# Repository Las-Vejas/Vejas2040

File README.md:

# Vejas2040
an RP2040 devboard made by me

What it includes:
- RP2040
- 1 Neopixel LED
- 2 buttons
- a pico form factor

Here are some images of the board (3d files):

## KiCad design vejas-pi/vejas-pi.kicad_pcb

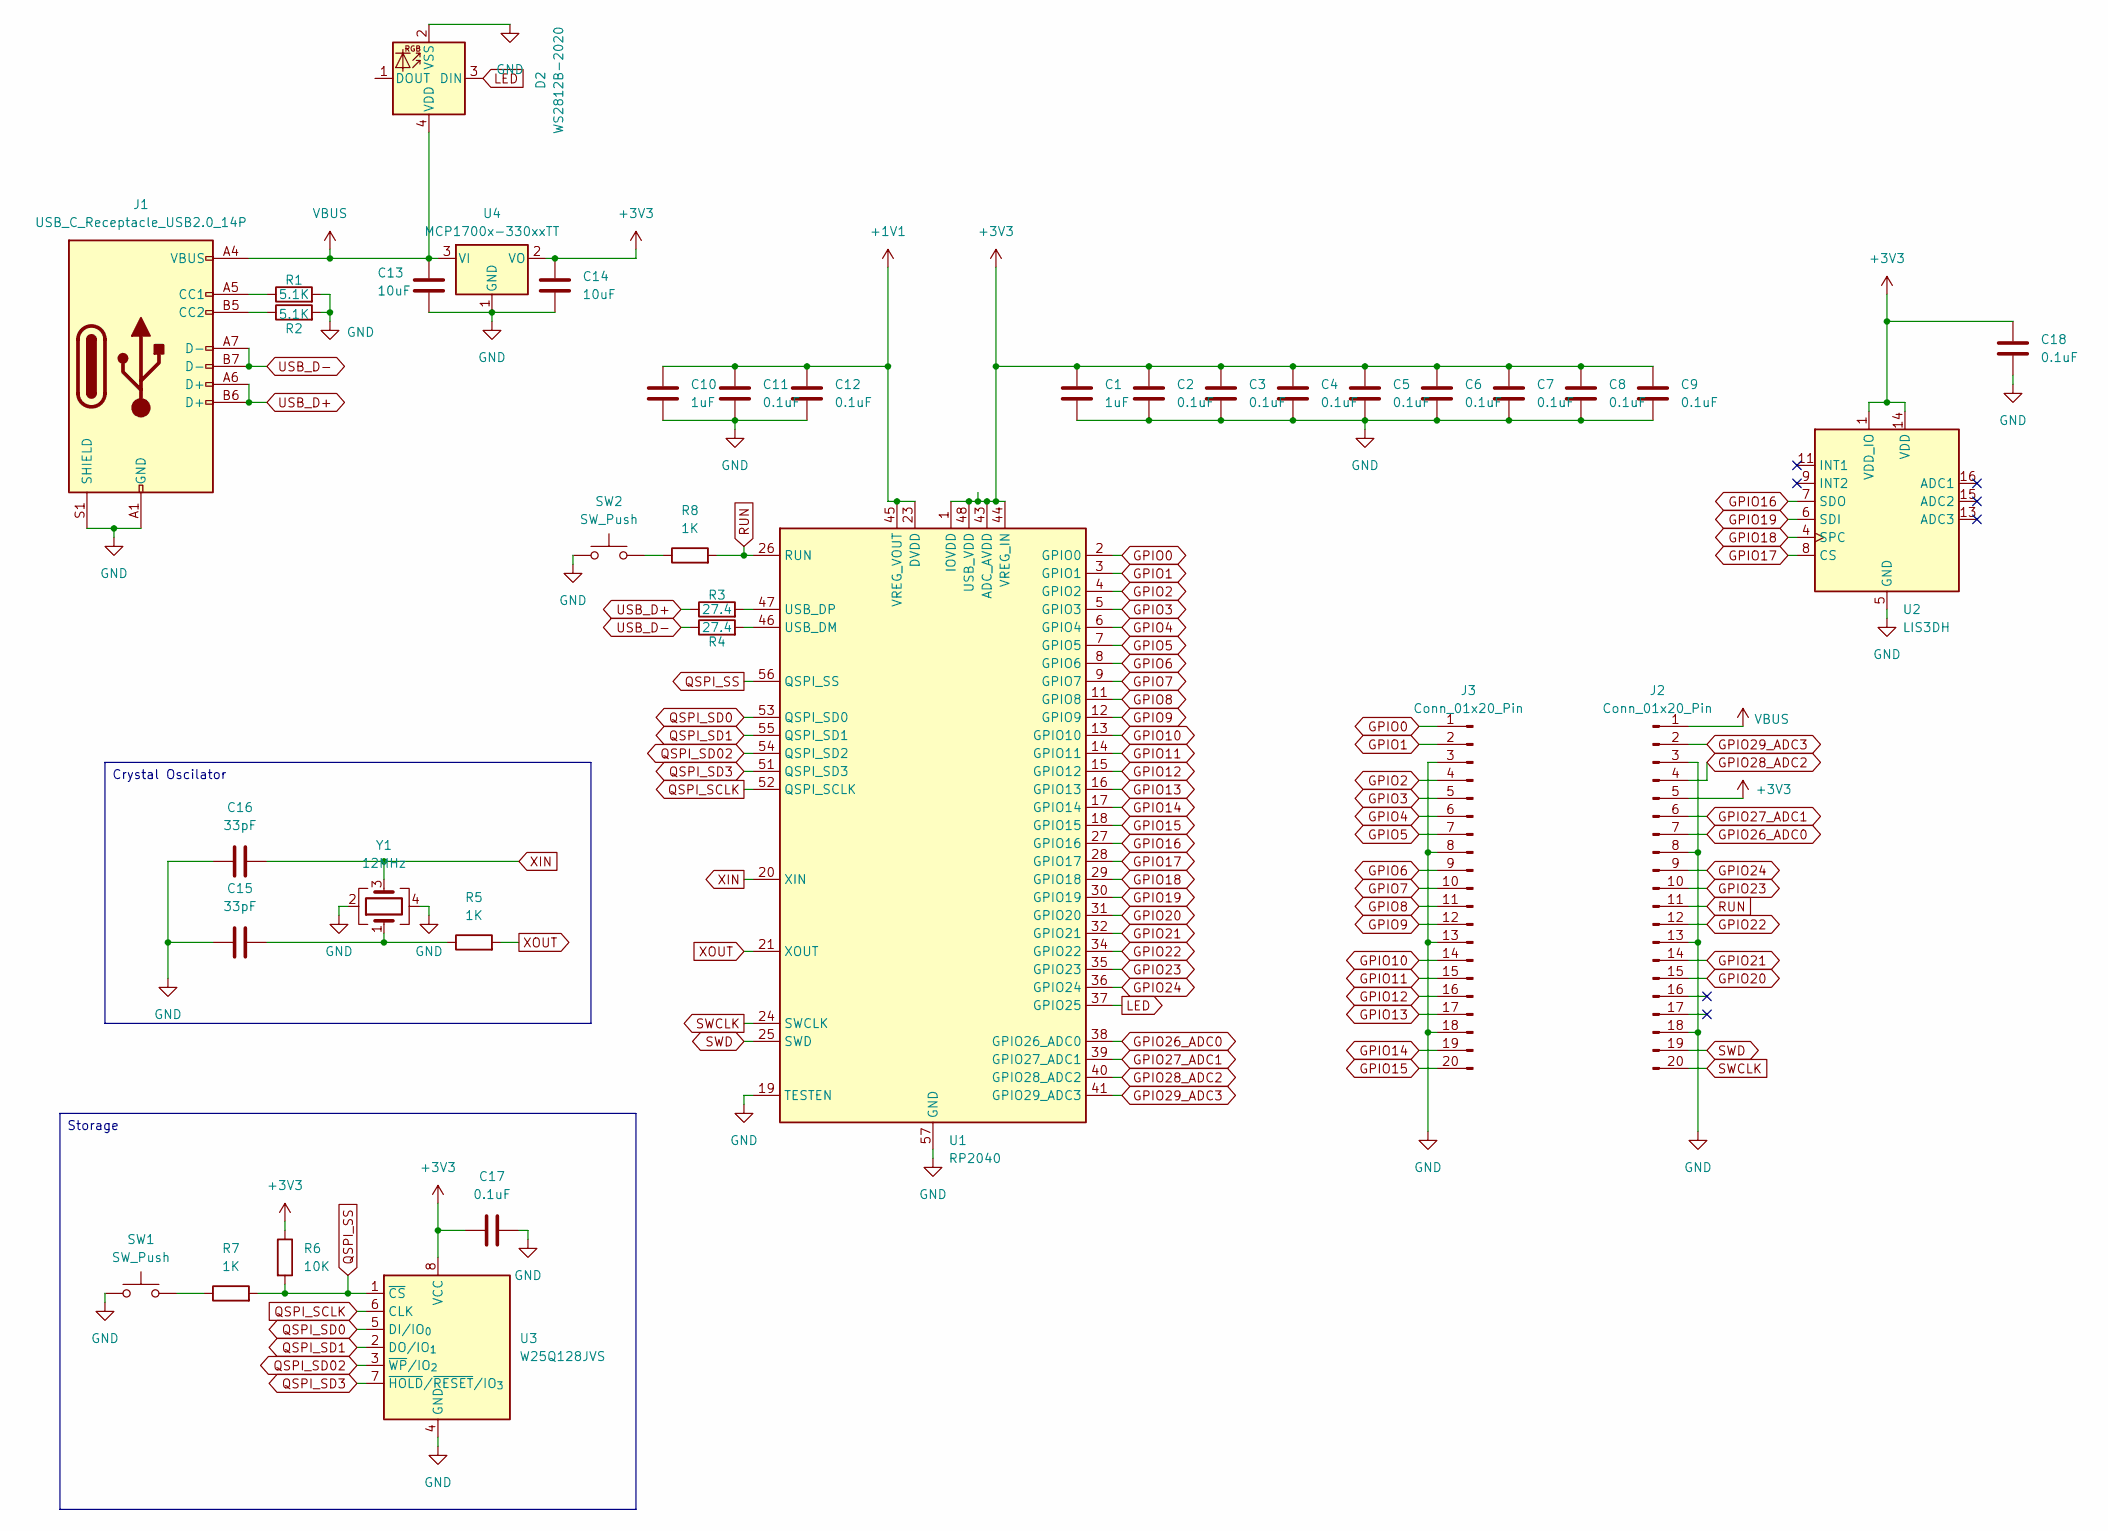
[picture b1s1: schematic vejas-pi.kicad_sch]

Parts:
C1, C10: 1uF; C_0402_1005Metric
C2, C3, C4, C5, C6, C7, C8, C9, C11, C12, C17, C18: 0.1uF; C_0402_1005Metric
C13, C14: 10uF; C_0603_1608Metric
C15, C16: 33pF; C_0402_1005Metric
D2: WS2812B-2020; LED_WS2812B-2020_PLCC4_2.0x2.0mm
J1: USB_C_Receptacle_USB2.0_14P; USB_C_Receptacle_JAE_DX07S016JA1R1500
J2, J3: Conn_01x20_Pin; PinHeader_1x20_P2.54mm_Vertical
R1, R2: 5.1K; R_0402_1005Metric
R3, R4: 27.4; R_0402_1005Metric
R5, R7, R8: 1K; R_0402_1005Metric
R6: 10K; R_0402_1005Metric
SW1, SW2: SW_Push; SW_Push_SPST_NO_Alps_SKRK
U1: RP2040; QFN-56-1EP_7x7mm_P0.4mm_EP3.2x3.2mm
U2: LIS3DH; LGA-16_3x3mm_P0.5mm_LayoutBorder3x5y
U3: W25Q128JVS; Winbond_USON-8-1EP_3x2mm_P0.5mm_EP0.2x1.6mm
U4: MCP1700x-330xxTT; SOT-23
Y1: 12MHz; Crystal_SMD_3225-4Pin_3.2x2.5mm

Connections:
+1V1: C10.1, C11.1, C12.1, U1.23 (DVDD), U1.45 (VREG_VOUT), U1.50 (DVDD)
+3V3: C1.1, C2.1, C3.1, C4.1, C5.1, C6.1, C7.1, C8.1, C9.1, C14.1, C17.1, C18.1, J2.5, R6.1, U1.1 (IOVDD), U1.10 (IOVDD), U1.22 (IOVDD), U1.33 (IOVDD), U1.42 (IOVDD), U1.43 (ADC_AVDD), U1.44 (VREG_IN), U1.48 (USB_VDD), U1.49 (IOVDD), U2.1 (VDD_IO), U2.14 (VDD), U3.8 (VCC), U4.2 (VO)
GND: C1.2, C2.2, C3.2, C4.2, C5.2, C6.2, C7.2, C8.2, C9.2, C10.2, C11.2, C12.2, C13.2, C14.2, C15.1, C16.1, C17.2, C18.2, D2.2 (VSS), J1.A1 (GND), J1.A12 (GND), J1.B1 (GND), J1.B12 (GND), J1.S1 (SHIELD), J2.3, J2.8, J2.13, J2.18, J3.3, J3.8, J3.13, J3.18, R1.2, R2.2, SW1.1, SW2.1, U1.19 (TESTEN), U1.57 (GND), U2.5 (GND), U2.10 (GND), U2.12 (GND), U3.4 (GND), U4.1 (GND), Y1.2, Y1.4
GPIO0: J3.1, U1.2 (GPIO0)
GPIO1: J3.2, U1.3 (GPIO1)
GPIO2: J3.4, U1.4 (GPIO2)
GPIO3: J3.5, U1.5 (GPIO3)
GPIO4: J3.6, U1.6 (GPIO4)
GPIO5: J3.7, U1.7 (GPIO5)
GPIO6: J3.9, U1.8 (GPIO6)
GPIO7: J3.10, U1.9 (GPIO7)
GPIO8: J3.11, U1.11 (GPIO8)
GPIO9: J3.12, U1.12 (GPIO9)
GPIO10: J3.14, U1.13 (GPIO10)
GPIO11: J3.15, U1.14 (GPIO11)
GPIO12: J3.16, U1.15 (GPIO12)
GPIO13: J3.17, U1.16 (GPIO13)
GPIO14: J3.19, U1.17 (GPIO14)
GPIO15: J3.20, U1.18 (GPIO15)
GPIO16: U1.27 (GPIO16), U2.7 (SDO)
GPIO17: U1.28 (GPIO17), U2.8 (CS)
GPIO18: U1.29 (GPIO18), U2.4 (SPC)
GPIO19: U1.30 (GPIO19), U2.6 (SDI)
GPIO20: J2.15, U1.31 (GPIO20)
GPIO21: J2.14, U1.32 (GPIO21)
GPIO22: J2.12, U1.34 (GPIO22)
GPIO23: J2.10, U1.35 (GPIO23)
GPIO24: J2.9, U1.36 (GPIO24)
GPIO26_ADC0: J2.7, U1.38 (GPIO26_ADC0)
GPIO27_ADC1: J2.6, U1.39 (GPIO27_ADC1)
GPIO28_ADC2: J2.4, U1.40 (GPIO28_ADC2)
GPIO29_ADC3: J2.2, U1.41 (GPIO29_ADC3)
LED: D2.3 (DIN), U1.37 (GPIO25)
unnamed: C15.2, R5.1, Y1.1
unnamed: J1.A5 (CC1), R1.1
unnamed: J1.B5 (CC2), R2.1
unnamed: R7.1, SW1.2
unnamed: R8.1, SW2.2
unnamed: R4.2, U1.46 (USB_DM)
unnamed: R3.2, U1.47 (USB_DP)
QSPI_SCLK: U1.52 (QSPI_SCLK), U3.6 (CLK)
QSPI_SD0: U1.53 (QSPI_SD0), U3.5 (DI/IO_{0})
QSPI_SD1: U1.55 (QSPI_SD1), U3.2 (DO/IO_{1})
QSPI_SD02: U1.54 (QSPI_SD2), U3.3 (~WP/IO_{2})
QSPI_SD3: U1.51 (QSPI_SD3), U3.7 (~HOLD/~RESET/IO_{3})
QSPI_SS: R6.2, R7.2, U1.56 (QSPI_SS), U3.1 (~CS)
RUN: J2.11, R8.2, U1.26 (RUN)
SWCLK: J2.20, U1.24 (SWCLK)
SWD: J2.19, U1.25 (SWD)
USB_D+: J1.A6 (D+), J1.B6 (D+), R3.1
USB_D-: J1.A7 (D-), J1.B7 (D-), R4.1
VBUS: C13.1, D2.4 (VDD), J1.A4 (VBUS), J1.A9 (VBUS), J1.B4 (VBUS), J1.B9 (VBUS), J2.1, U4.3 (VI)
XIN: C16.2, U1.20 (XIN), Y1.3
XOUT: R5.2, U1.21 (XOUT)

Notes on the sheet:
Crystal Oscilator
Storage

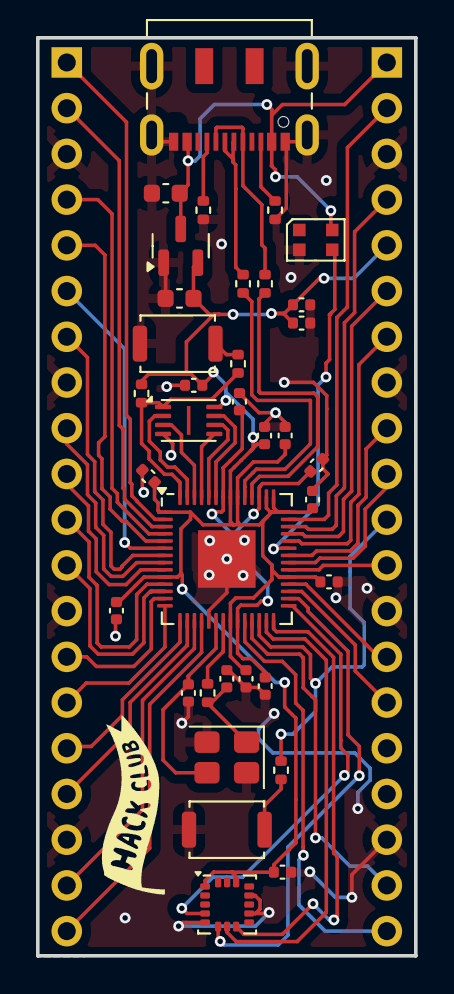
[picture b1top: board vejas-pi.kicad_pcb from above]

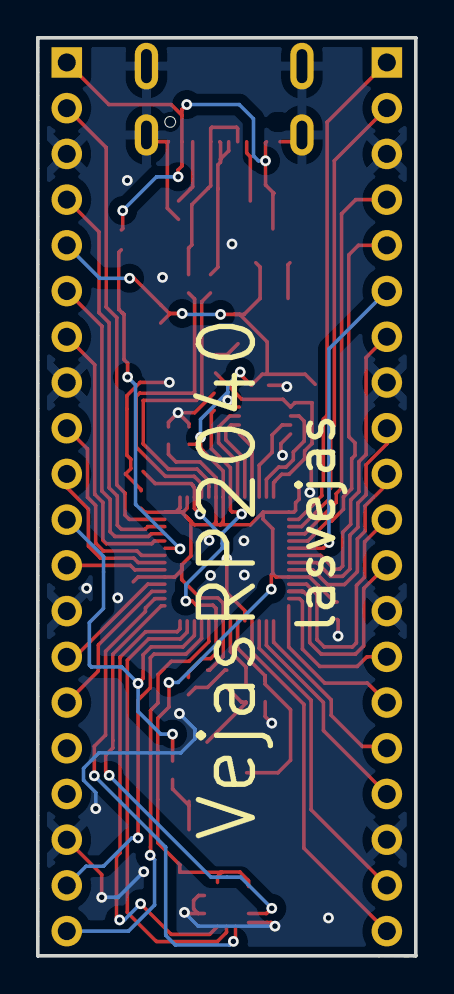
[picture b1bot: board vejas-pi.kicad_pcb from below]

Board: 2 copper layers, 21.0 x 51.0 mm, 37 parts (2 on the bottom side), 54 nets.

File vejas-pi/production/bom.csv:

Designator,Footprint,Quantity,Value,LCSC Part #
"C1, C10",0402,2,1uF,
"C11, C12, C17, C18, C2, C3, C4, C5, C6, C7, C8, C9",0402,12,0.1uF,
"C13, C14",0603,2,10uF,
"C15, C16",0402,2,33pF,
D2,LED_WS2812B-2020_PLCC4_2.0x2.0mm,1,WS2812B-2020,
J1,USB_C_Receptacle_JAE_DX07S016JA1R1500,1,USB_C_Receptacle_USB2.0_14P,
"J2, J3",PinHeader_1x20_P2.54mm_Vertical,2,Conn_01x20_Pin,
"R1, R2",0402,2,5.1K,
"R3, R4",0402,2,27.4,
"R5, R7, R8",0402,3,1K,
R6,0402,1,10K,
"SW1, SW2",SW_Push_SPST_NO_Alps_SKRK,2,SW_Push,
U1,QFN-56-1EP_7x7mm_P0.4mm_EP3.2x3.2mm,1,RP2040,
U2,LGA-16_3x3mm_P0.5mm_LayoutBorder3x5y,1,LIS3DH,
U3,Winbond_USON-8-1EP_3x2mm_P0.5mm_EP0.2x1.6mm,1,W25Q128JVS,
U4,SOT-23,1,MCP1700x-330xxTT,
Y1,Crystal_SMD_3225-4Pin_3.2x2.5mm,1,12MHz,

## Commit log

2025-10-05 git init
    added kicad files
2025-10-11 a lot of pcb
2025-10-11 pcb v1
2025-10-12 Add images of the board to README
    Added images of the board to the README.
2025-10-16 edits
2025-10-17 very kul
2025-10-24 cool stuff V1.1 SHIPPED
2025-10-25 Update BOM format and item prices
2025-11-22 Fix header row in bom-digikey.csv
    Updated the header row in the BOM CSV file to include the correct column names.
2025-11-22 Change BOM delimiter from semicolon to comma
    Updated the BOM format to use commas instead of semicolons for better compatibility.
2025-11-22 Fix BOM header formatting in bom-digikey.csv
2025-11-22 Initial plan
2025-11-22 Fix CSV: remove extra header and quote reference designators
